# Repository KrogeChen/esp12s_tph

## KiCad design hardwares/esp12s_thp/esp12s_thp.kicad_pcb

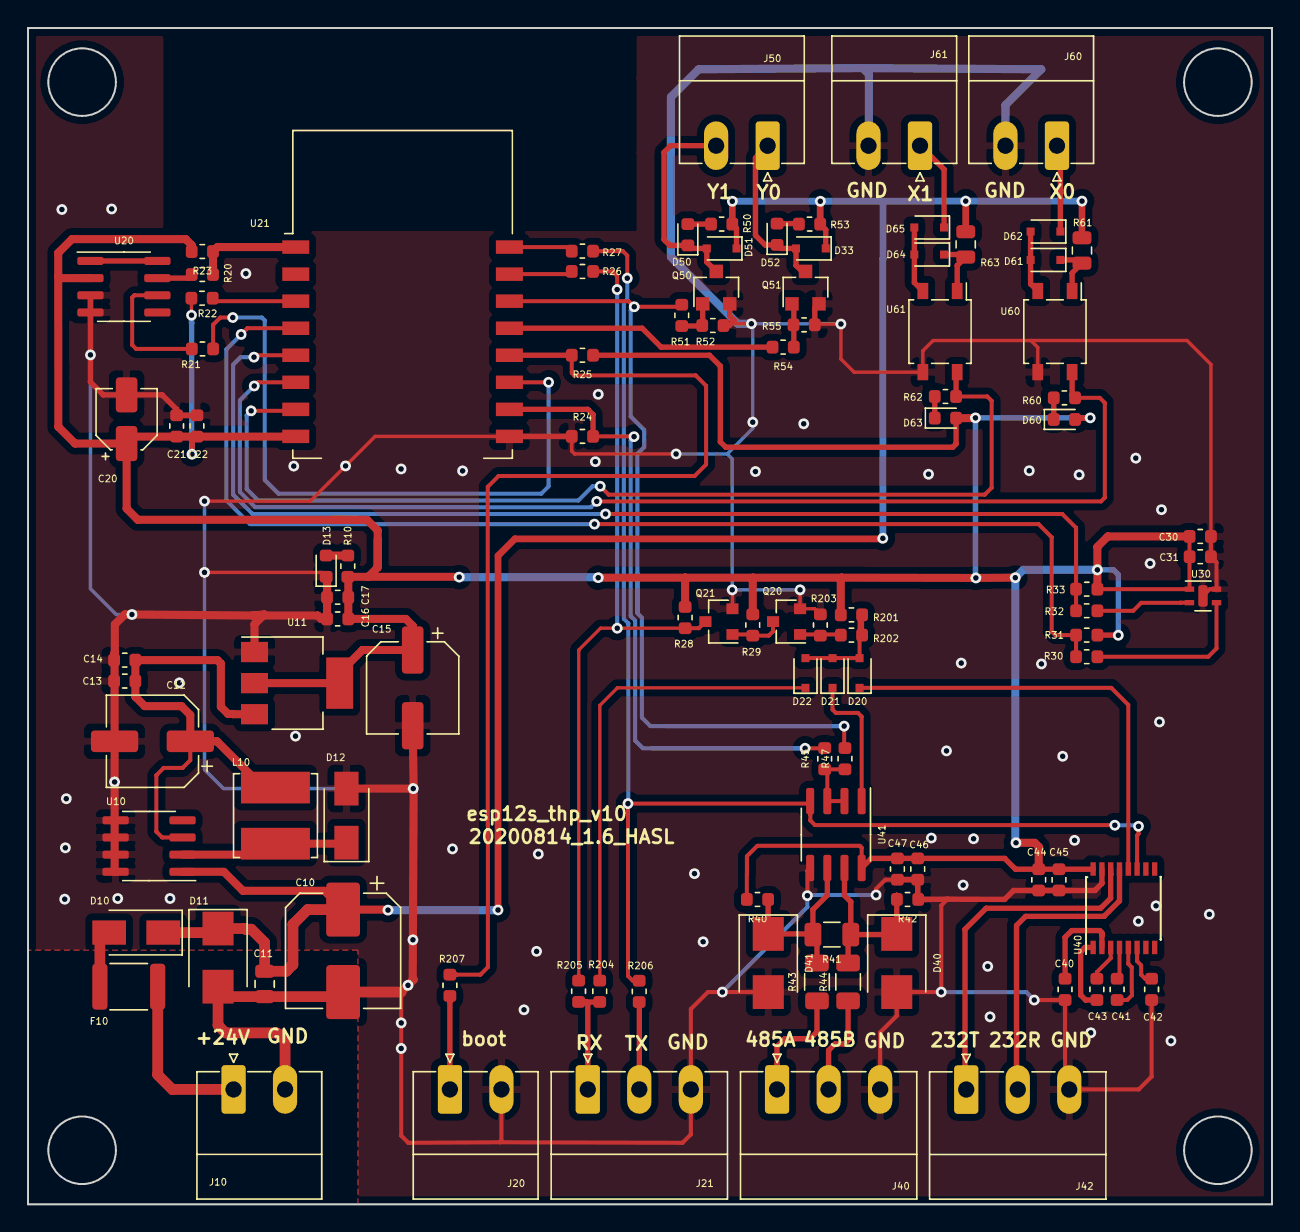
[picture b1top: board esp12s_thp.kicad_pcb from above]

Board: 2 copper layers, 92.0 x 87.0 mm, 102 parts (0 on the bottom side), 64 nets.

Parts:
C10: 47uF; CP_Elec_8x6.5
C11: 1uF; C_0805_2012Metric
C12, C15: 220uF; CP_Elec_6.3x5.4
C13, C16, C22, C30, C44, C47: 1uF; C_0603_1608Metric
C14, C17, C21, C31, C40, C41, C42, C43, C45, C46: 100nF; C_0603_1608Metric
C20: 47uF; CP_Elec_4x5.4
D10, D12: SS14; D_SMA
D11: SMBJ28A; D_SMB
D13: Red; LED_0603_1608Metric
D20, D21, D22, D33, D51, D61, D62, D64, D65: 1N4148; D_SOD-323F
D40, D41: SMBJ12A; D_SMB
D50, D52, D60, D63: Red; D_0603_1608Metric
F10: 200mA; Fuse_1812_4532Metric
J10: Power; PhoenixContact_MC_1,5_2-G-3.81_1x02_P3.81mm_Horizontal
J20: BOOT; PhoenixContact_MC_1,5_2-G-3.81_1x02_P3.81mm_Horizontal
J21: TTL; PhoenixContact_MC_1,5_3-G-3.81_1x03_P3.81mm_Horizontal
J40: 485; PhoenixContact_MC_1,5_3-G-3.81_1x03_P3.81mm_Horizontal
J42: 232; PhoenixContact_MC_1,5_3-G-3.81_1x03_P3.81mm_Horizontal
J50: YOUT; PhoenixContact_MC_1,5_2-G-3.81_1x02_P3.81mm_Horizontal
J60, J61: XIN; PhoenixContact_MC_1,5_2-G-3.81_1x02_P3.81mm_Horizontal
L10: 68uH; L_Bourns_SRN6045TA
Q20, Q21: SS8050; SOT-23
Q50, Q51: AO3422; SOT-23_big
R10, R52, R55, R60, R62: 2.7k; R_0603_1608Metric
R20, R21, R26, R27, R30, R32, R45, R51, R54, R204, R206, R207: 33R; R_0603_1608Metric
R22, R23, R24, R25, R31, R33, R40, R42: 10k; R_0603_1608Metric
R28, R29, R201, R202, R203: 4.7k; R_0603_1608Metric
R41: NP_120; R_1206_3216Metric
R43, R44: 20; R_1206_3216Metric
R47, R205: NP; R_0603_1608Metric
R50, R53: 33k; R_0603_1608Metric
R61, R63: 7.5k; R_0805_2012Metric
U10: XL1509; SOIC-8_3.9x4.9mm_P1.27mm
U11: LM1117-3.3; SOT-223
U20: SP706S; SOIC-8_3.9x4.9mm_P1.27mm
U21: ESP-12S
U30: SHTC3
U40: SP3232; SSOP-16_4.4x5.2mm_P0.65mm
U41: SP3485CN; SOIC-8_3.9x4.9mm_P1.27mm
U60, U61: EL357N; SO-4_4.4x4.3mm_P2.54mm

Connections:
+5VD: C12.1, C13.1, C14.1, L10.2, U10.3, U11.3
/BOOT: R25.2, R207.2, U21.12
/M_RX: R26.2, U21.15
/M_TX: R27.2, U21.16
/M_X0: R60.2, U21.6, U60.4
/M_X1: R62.2, U21.7, U61.4
/M_Y0: R54.2, U21.13
/M_Y1: R47.2, R51.2, U21.14
/M_Y2: R24.2, R45.2, U21.10
/RS1_A: J40.1, R43.1
/RS1_B: J40.2, R44.1
/RS2_R: J42.2, U40.13
/RS2_T: J42.1, U40.14
/RST: R20.1, R23.1, U21.1
/RX1: D20.1, U40.12
/RX2: D21.1, U41.1
/RX3: D22.1, R204.2
/RXD: Q21.3, R26.1, R28.1, R205.2
/SCL: R32.1, R33.1, U21.5
/SDA: R30.2, R31.1, U21.4
/TR_S1: R45.1, R47.1, U41.2, U41.3
/TXD: R27.1, R206.2, U40.11, U41.4
/VIN: F10.1, J10.1
/WDT: R21.1, U21.11
/X0: D62.1, J60.1
/X1: D65.1, J61.1
/Y0: D33.2, D52.1, J50.1, Q51.3
/Y1: D50.1, D51.2, J50.2, Q50.3
GND: C10.2, C11.2, C12.2, C13.2, C14.2, C15.2, C16.2, C17.2, C20.2, C21.1, C22.1, C30.2, C31.2, C42.2, C43.2, C44.2, C45.1, C46.2, C47.2, D11.2, D12.2, D13.1, D40.2, D41.2, J10.2, J20.2, J21.3, J40.3, J42.3, J60.2, J61.2, Q20.2, Q21.2, Q50.2, Q51.2, R24.1, R42.1, R52.2, R55.2, R203.1, U10.5, U10.6, U10.7, U10.8, U11.1, U20.3, U20.4, U21.9, U30.4, U30.5, U40.15, U41.5, U60.3, U61.3
unnamed: C40.1, U40.1
unnamed: C40.2, U40.3
unnamed: C41.1, U40.4
unnamed: C41.2, U40.5
unnamed: C42.1, U40.6
unnamed: C43.1, U40.2
unnamed: D10.2, F10.2
unnamed: D12.1, L10.1, U10.2
unnamed: D13.2, R10.1
unnamed: D20.2, D21.2, D22.2, R201.2, R202.1
unnamed: D40.1, R41.1, R42.2, R44.2, U41.7
unnamed: D41.1, R40.1, R41.2, R43.2, U41.6
unnamed: D50.2, R50.1
unnamed: D52.2, R53.1
unnamed: D60.1, R60.1
unnamed: D61.1, R61.1, U60.1
unnamed: D61.2, D62.2, U60.2
unnamed: D63.1, R62.1
unnamed: D64.1, R63.1, U61.1
unnamed: D64.2, D65.2, U61.2
unnamed: J20.1, R207.1
unnamed: J21.1, R204.1, R205.1
unnamed: J21.2, R206.1
unnamed: Q20.1, R202.2, R203.2
unnamed: Q20.3, Q21.1, R29.1
unnamed: Q50.1, R51.1, R52.1
unnamed: Q51.1, R54.1, R55.1
unnamed: R20.2, U20.7
unnamed: R21.2, U20.6
unnamed: R22.1, U21.3
unnamed: R30.1, U30.3
unnamed: R32.2, U30.2
unnamed: U20.1, U20.8
VCC: C15.1, C16.1, C17.1, C20.1, C21.2, C22.2, C30.1, C31.1, C44.1, C45.2, C46.1, C47.1, D60.2, D63.2, R10.2, R22.2, R23.2, R25.1, R28.2, R29.2, R31.2, R33.2, R40.2, R201.1, U11.2, U11.4, U20.2, U21.8, U30.1, U40.16, U41.8
VDD: C10.1, C11.1, D10.1, D11.1, D33.1, D51.1, R50.2, R53.2, R61.2, R63.2, U10.1

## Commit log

2020-09-22 frist design
2020-09-22 frist complied
